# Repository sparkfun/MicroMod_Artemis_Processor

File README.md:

SparkFun MicroMod Artemis Processor Board
========================================

[*SparkFun MicroMod Artemis Processor Board (16401)*](https://www.sparkfun.com/products/16401)

Leveraging the ultra powerful Artemis Module, the SparkFun MicroMod Artemis Processor is the brain board of your dreams. Need Machine Learning capabilities? We gotcha. Need Bluetooth? We gotcha. Need I<sup>2</sup>C functionality to connect to all our amazing Qwiic boards? We totally gotcha.  

At the heart of SparkFun's Artemis module is Ambiq Micro's Apollo3 processor, whose ultra-efficient ARM Cortex-M4F processor is spec’d to run TensorFlow Lite using only 6uA/MHz. We've routed 2 I<sup>2</sup>C buses, 8 GPIO, dedicated digital, analog, and PWM pins, multiple SPI as well as QuadSPI, and Bluetooth to boot. You really can't go wrong with this processor. Grab one today, pick up a compatible carrier board, and get hacking! 

Repository Contents
-------------------

* **/Hardware** - Eagle design files (.brd, .sch)
* **/TestSketches** - Related software for the MicroMod Artemis Processor Board

Documentation
--------------
* **[Hookup Guide](https://learn.sparkfun.com/tutorials/micromod-artemis-processor-board-hookup-guide)** - Basic hookup guide for the MicroMod Artemis Processor Board.
* **[Getting Started with MicroMod](https://learn.sparkfun.com/tutorials/getting-started-with-micromod)** - A tutorial to help you get started with the MicroMod Ecosystem. 
* **[Designing with MicroMod](https://learn.sparkfun.com/tutorials/designing-with-micromod)** - A tutorial to walk you through the specs of the MicroMod processor and carrier board as well as the basics of incorporating the MicroMod form factor into your own PCB designs.

License Information
-------------------

This product is _**open source**_! 

Please review the LICENSE.md file for license information. 

If you have any questions or concerns on licensing, please contact technical support on our [SparkFun forums](https://forum.sparkfun.com/viewforum.php?f=152).

Distributed as-is; no warranty is given.

- Your friends at SparkFun.

_<COLLABORATION CREDIT>_

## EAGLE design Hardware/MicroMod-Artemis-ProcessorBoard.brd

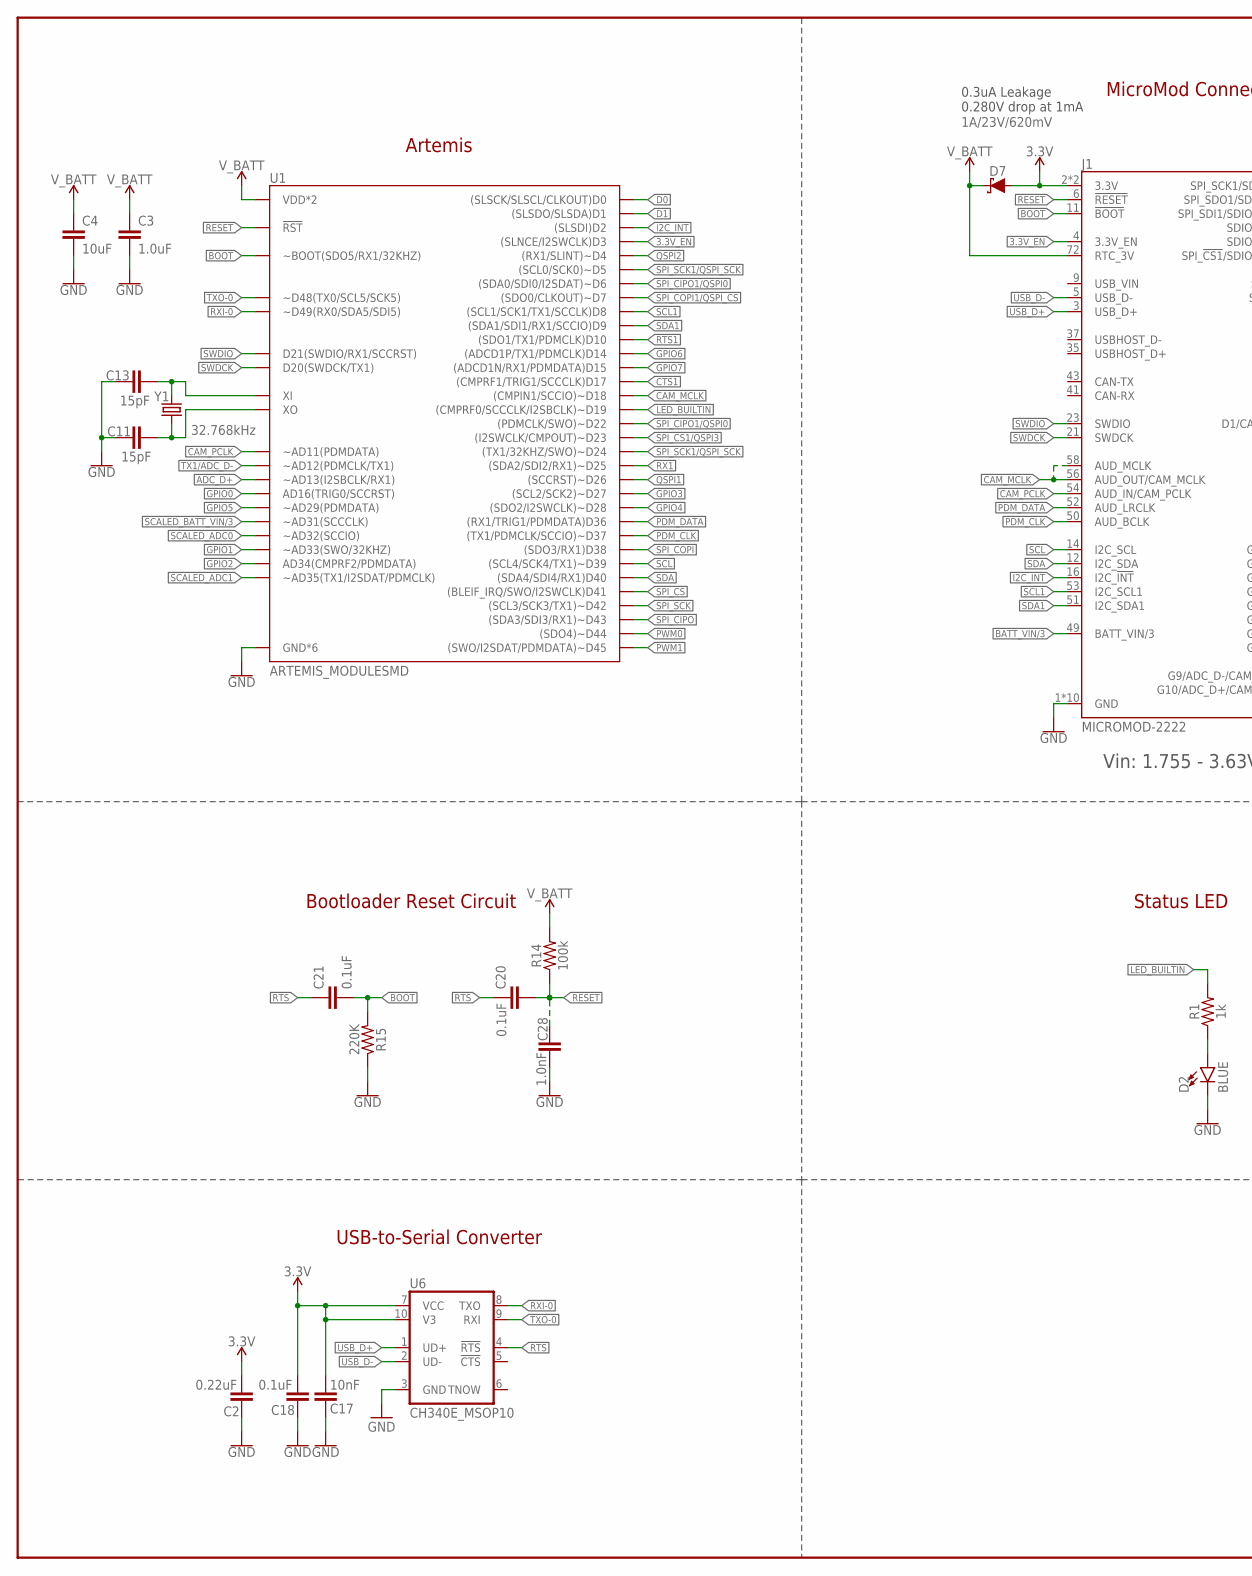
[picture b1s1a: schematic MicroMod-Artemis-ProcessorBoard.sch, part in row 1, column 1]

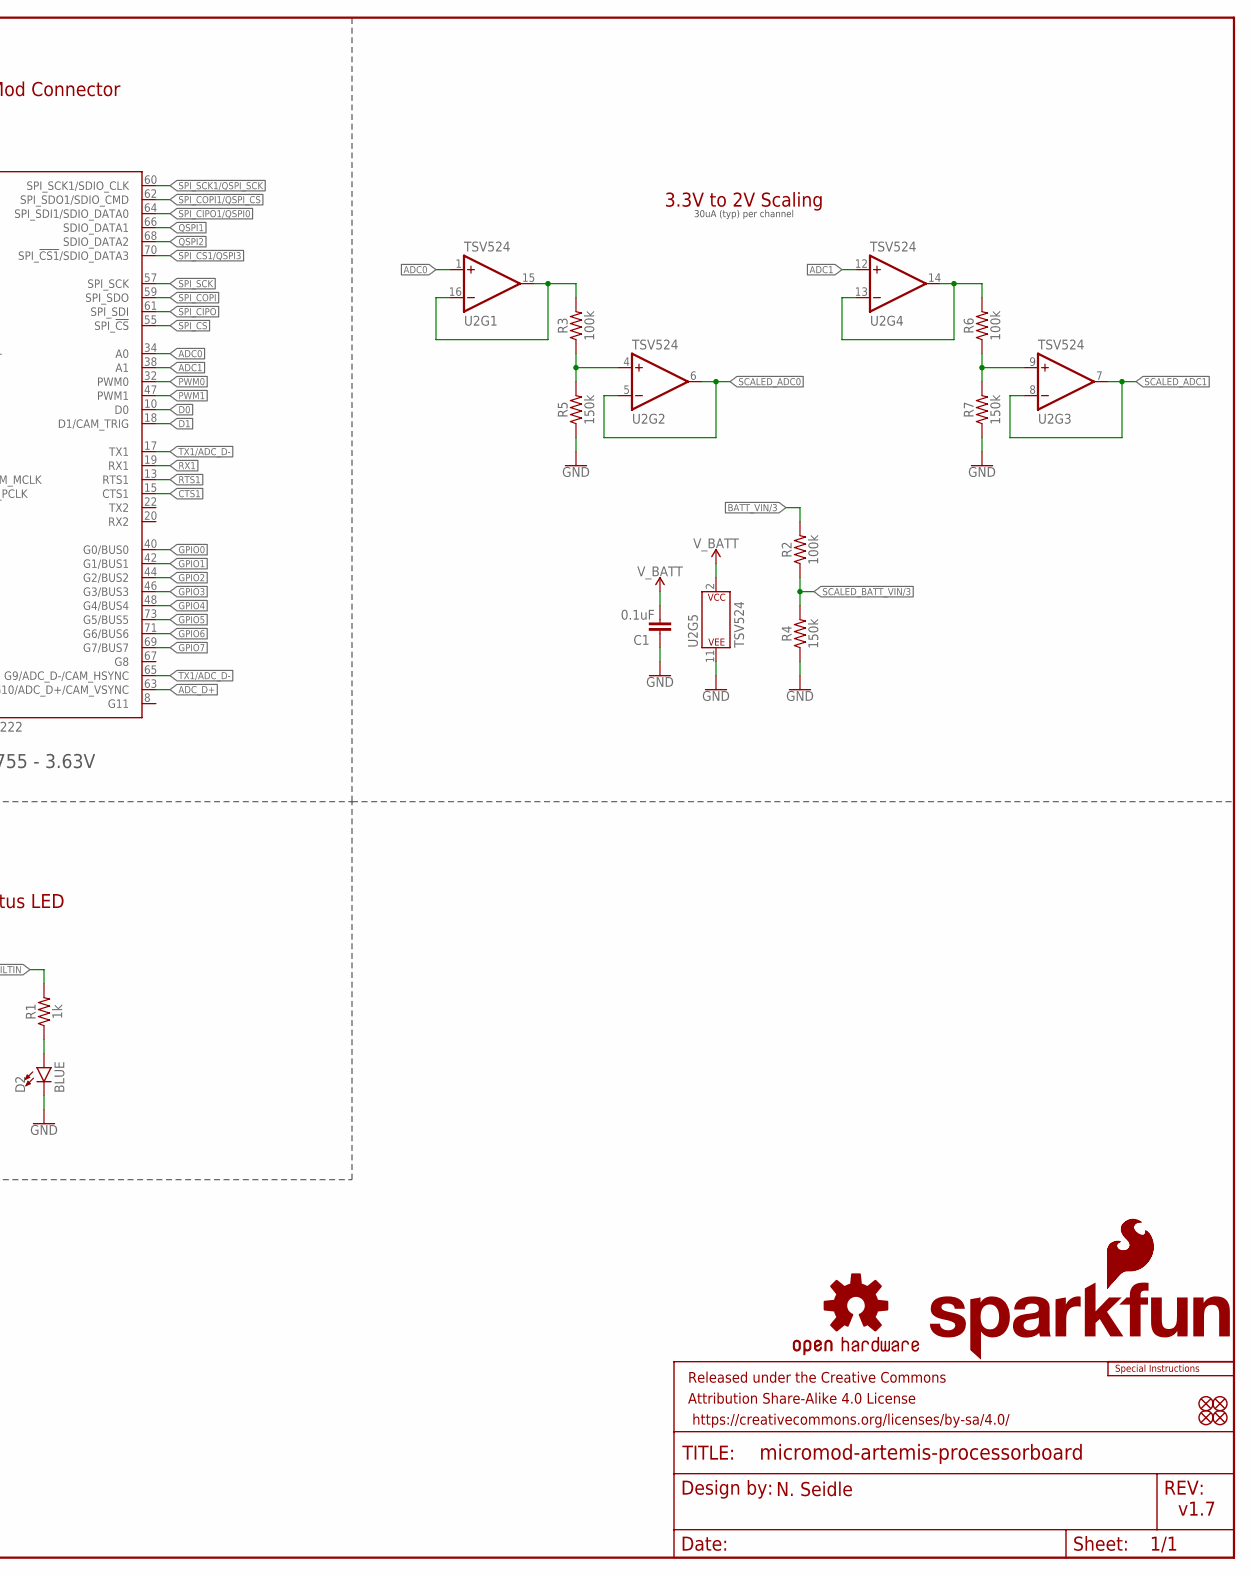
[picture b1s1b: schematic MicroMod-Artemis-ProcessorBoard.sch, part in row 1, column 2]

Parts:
C1, C18, C20, C21: 0.1uF; 0402-TIGHT
C2: 0.22uF; 0402-TIGHT
C3: 1.0uF; 0402-TIGHT
C4: 10uF; 0603
C11, C13: 15pF; 0402-TIGHT
C17: 10nF; 0402-TIGHT
C28: 1.0nF; 0402-TIGHT
D2: BLUE; LED-0603
D7: 1A/23V/620mV; SOD-323
FD1, FD2, FD3, FD4: FIDUCIALUFIDUCIAL; FIDUCIAL-MICRO
FRAME1: FRAME-LEDGER; CREATIVE_COMMONS
J1: MICROMOD-2222; M.2-CARD-E-22
LOGO1: SFE_LOGO_NAME_FLAME.1_INCH; SFE_LOGO_NAME_FLAME_.1
LOGO2: SFE_LOGO_FLAME.1_INCH; SFE_LOGO_FLAME_.1
LOGO3: OSHW-LOGOMINI; OSHW-LOGO-MINI
LOGO4: SPECIAL_INSTRUCTIONS-ORDERING; ORDERING_INSTRUCTIONS
R1: 1k; 0402-TIGHT
R2, R3, R6, R14: 100k; 0402-TIGHT
R4, R5, R7: 150k; 0402-TIGHT
R15: 220K; 0402-TIGHT
U1: ARTEMIS_MODULESMD; ARTEMIS_FP
U2: TSV524; QFN-16
U6: CH340E_MSOP10; MSOP10
Y1: 32.768kHz; CRYSTAL-SMD-3.2X1.5MM

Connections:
3.3V: C2.1, C17.1, C18.1, D7.A, J1.2 (3.3V), J1.74 (3.3V), U6.7 (VCC), U6.10 (V3)
3.3V_EN: J1.4 (3.3V_EN), U1.D3 ((SLNCE/I2SWCLK)D3)
!RESET!: C20.2, C28.1, J1.6 (!RESET!), R14.1, U1.~RST (!RST)
!RTS: C20.1, C21.1, U6.4 (!RTS)
ADC0: J1.34 (A0), U2.1 (+IN)
ADC0_BUFF1: R3.2, U2.15 (OUT), U2.16 (-IN)
ADC0_BUFF2: R3.1, R5.2, U2.4 (+IN)
ADC1: J1.38 (A1), U2.12 (+IN)
ADC1_BUFF2: R6.1, R7.2, U2.9 (+IN)
ADC_BUFF1: R6.2, U2.13 (-IN), U2.14 (OUT)
ADC_D+: J1.63 (G10/ADC_D+/CAM_VSYNC), U1.~AD13 (~AD13(I2SBCLK/RX1))
BATT_VIN/3: J1.49 (BATT_VIN/3), R2.2
BOOT: C21.2, J1.11 (!BOOT!), R15.2, U1.BOOT (~BOOT(SDO5/RX1/32KHZ))
CAM_MCLK: J1.56 (AUD_OUT/CAM_MCLK), J1.58 (AUD_MCLK), U1.~D18 ((CMPIN1/SCCIO)~D18)
CAM_PCLK: J1.54 (AUD_IN/CAM_PCLK), U1.~AD11 (~AD11(PDMDATA))
CTS1: J1.15 (CTS1), U1.D17 ((CMPRF1/TRIG1/SCCCLK)D17)
D0: J1.10 (D0), U1.D0 ((SLSCK/SLSCL/CLKOUT)D0)
D1: J1.18 (D1/CAM_TRIG), U1.D1 ((SLSDO/SLSDA)D1)
GND: C1.2, C2.2, C3.2, C4.2, C11.1, C13.1, C17.2, C18.2, C28.2, D2.C, J1.1 (GND), J1.7 (GND), J1.33 (GND), J1.36 (GND), J1.39 (GND), J1.45 (GND), J1.75 (GND), J1.GND1 (GND), J1.GND2 (GND), J1.GND3 (GND), R4.1, R5.1, R7.1, R15.1, U1.GND@1 (GND*6), U1.GND@22 (GND*6), U1.GND@38 (GND*6), U1.GND@39 (GND*6), U1.GND@47 (GND*6), U1.GND@59 (GND*6), U2.11 (V-), U6.3 (GND)
GPIO0: J1.40 (G0/BUS0), U1.AD16 (AD16(TRIG0/SCCRST))
GPIO1: J1.42 (G1/BUS1), U1.~AD33/SWO (~AD33(SWO/32KHZ))
GPIO2: J1.44 (G2/BUS2), U1.AD34 (AD34(CMPRF2/PDMDATA))
GPIO3: J1.46 (G3/BUS3), U1.~D27 ((SCL2/SCK2)~D27)
GPIO4: J1.48 (G4/BUS4), U1.~D28 ((SDO2/I2SWCLK)~D28)
GPIO5: J1.73 (G5/BUS5), U1.~AD29 (~AD29(PDMDATA))
GPIO6: J1.71 (G6/BUS6), U1.D14 ((ADCD1P/TX1/PDMCLK)D14)
GPIO7: J1.69 (G7/BUS7), U1.D15 ((ADCD1N/RX1/PDMDATA)D15)
I2C_!INT!: J1.16 (I2C_!INT!), U1.D2 ((SLSDI)D2)
LED_BUILTIN: R1.2, U1.~D19 ((CMPRF0/SCCCLK/I2SBCLK)~D19)
unnamed: D2.A, R1.1
unnamed: C13.2, U1.XI, Y1.P$1 (1)
unnamed: C11.2, U1.XO, Y1.P$2 (2)
PDM_CLK: J1.50 (AUD_BCLK), U1.~D37 ((TX1/PDMCLK/SCCIO)~D37)
PDM_DATA: J1.52 (AUD_LRCLK), U1.D36 ((RX1/TRIG1/PDMDATA)D36)
PWM0: J1.32 (PWM0), U1.~D44 ((SDO4)~D44)
PWM1: J1.47 (PWM1), U1.~D45 ((SWO/I2SDAT/PDMDATA)~D45)
QSPI1: J1.66 (SDIO_DATA1), U1.~D26 ((SCCRST)~D26)
QSPI2: J1.68 (SDIO_DATA2), U1.~D4 ((RX1/SLINT)~D4)
RTS1: J1.13 (RTS1), U1.D10 ((SDO1/TX1/PDMCLK)D10)
RX1: J1.19 (RX1), U1.~D25 ((SDA2/SDI2/RX1)~D25)
RXI-0: U1.RXI-0 (~D49(RX0/SDA5/SDI5)), U6.8 (TXO)
SCALED_ADC0: U1.~AD32 (~AD32(SCCIO)), U2.5 (-IN), U2.6 (OUT)
SCALED_ADC1: U1.~AD35 (~AD35(TX1/I2SDAT/PDMCLK)), U2.7 (OUT), U2.8 (-IN)
SCALED_BATT_VIN/3: R2.1, R4.2, U1.~AD31 (~AD31(SCCCLK))
SCL: J1.14 (I2C_SCL), U1.~D39 ((SCL4/SCK4/TX1)~D39)
SCL1: J1.53 (I2C_SCL1), U1.D8 ((SCL1/SCK1/TX1/SCCLK)D8)
SDA: J1.12 (I2C_SDA), U1.D40 ((SDA4/SDI4/RX1)D40)
SDA1: J1.51 (I2C_SDA1), U1.D9 ((SDA1/SDI1/RX1/SCCIO)D9)
SPI_!CS1!/QSPI3: J1.70 (SPI_!CS1!/SDIO_DATA3), U1.~D23 ((I2SWCLK/CMPOUT)~D23)
SPI_!CS!: J1.55 (SPI_!CS!), U1.D41 ((BLEIF_IRQ/SWO/I2SWCLK)D41)
SPI_CIPO: J1.61 (SPI_SDI), U1.~D43 ((SDA3/SDI3/RX1)~D43)
SPI_CIPO1/QSPI0: J1.64 (SPI_SDI1/SDIO_DATA0), U1.~D6 ((SDA0/SDI0/I2SDAT)~D6), U1.~D22 ((PDMCLK/SWO)~D22)
SPI_COPI: J1.59 (SPI_SDO), U1.D38 ((SDO3/RX1)D38)
SPI_COPI1/QSPI_!CS!: J1.62 (SPI_SDO1/SDIO_CMD), U1.D7 ((SDO0/CLKOUT)~D7)
SPI_SCK: J1.57 (SPI_SCK), U1.~D42 ((SCL3/SCK3/TX1)~D42)
SPI_SCK1/QSPI_SCK: J1.60 (SPI_SCK1/SDIO_CLK), U1.~D5 ((SCL0/SCK0)~D5), U1.~D24 ((TX1/32KHZ/SWO)~D24)
SWDCK: J1.21 (SWDCK), U1.SWDCK (D20(SWDCK/TX1))
SWDIO: J1.23 (SWDIO), U1.SWDIO (D21(SWDIO/RX1/SCCRST))
TX1/ADC_D-: J1.17 (TX1), J1.65 (G9/ADC_D-/CAM_HSYNC), U1.~AD12 (~AD12(PDMCLK/TX1))
TXO-0: U1.TXO-0 (~D48(TX0/SCL5/SCK5)), U6.9 (RXI)
USB_D+: J1.3 (USB_D+), U6.1 (UD+)
USB_D-: J1.5 (USB_D-), U6.2 (UD-)
V_BATT: C1.1, C3.1, C4.1, D7.C, J1.72 (RTC_3V), R14.2, U1.VDD@36 (VDD*2), U1.VDD@37 (VDD*2), U2.2 (V+)

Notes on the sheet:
USB-to-Serial Converter
Bootloader Reset Circuit
MicroMod Connector
3.3V to 2V Scaling
v1.7
N. Seidle
Artemis
Status LED
Vin: 1.755 - 3.63V
0.3uA Leakage 0.280V drop at 1mA
30uA (typ) per channel

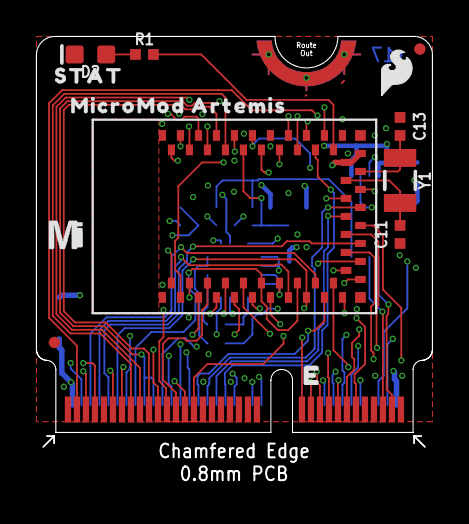
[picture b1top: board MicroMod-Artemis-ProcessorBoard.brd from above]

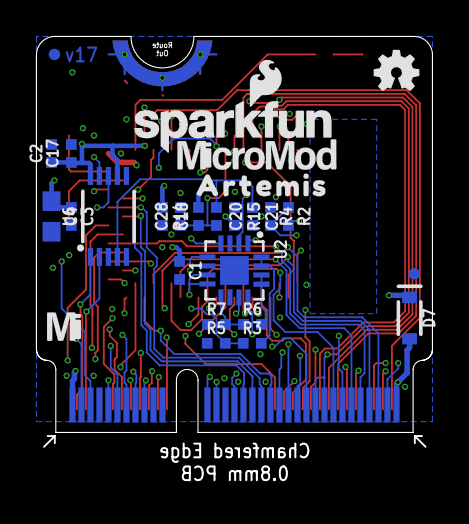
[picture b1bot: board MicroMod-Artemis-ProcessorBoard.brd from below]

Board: 4 copper layers, 22.0 x 22.8 mm, 42 parts (27 on the bottom side), 63 nets.

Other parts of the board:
U$1, U$7: MICROMOD_MI_LOGO_.35
U$5: MICROMOD_LOGO_.35
U$8: MICROMOD_ARTEMIS0
U$9: ARTEMIS0
U$11: STAT0

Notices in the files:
parts and their libraries:
SparkFun-IC-Microcontroller: Licensing: Creative Commons ShareAlike 4.0 International - https://creativecommons.org/licenses/by-sa/4.0
SparkFun-Aesthetics: Released under the Creative Commons Attribution Share-Alike 4.0 License
SparkFun-Aesthetics: https://creativecommons.org/licenses/by-sa/4.0
